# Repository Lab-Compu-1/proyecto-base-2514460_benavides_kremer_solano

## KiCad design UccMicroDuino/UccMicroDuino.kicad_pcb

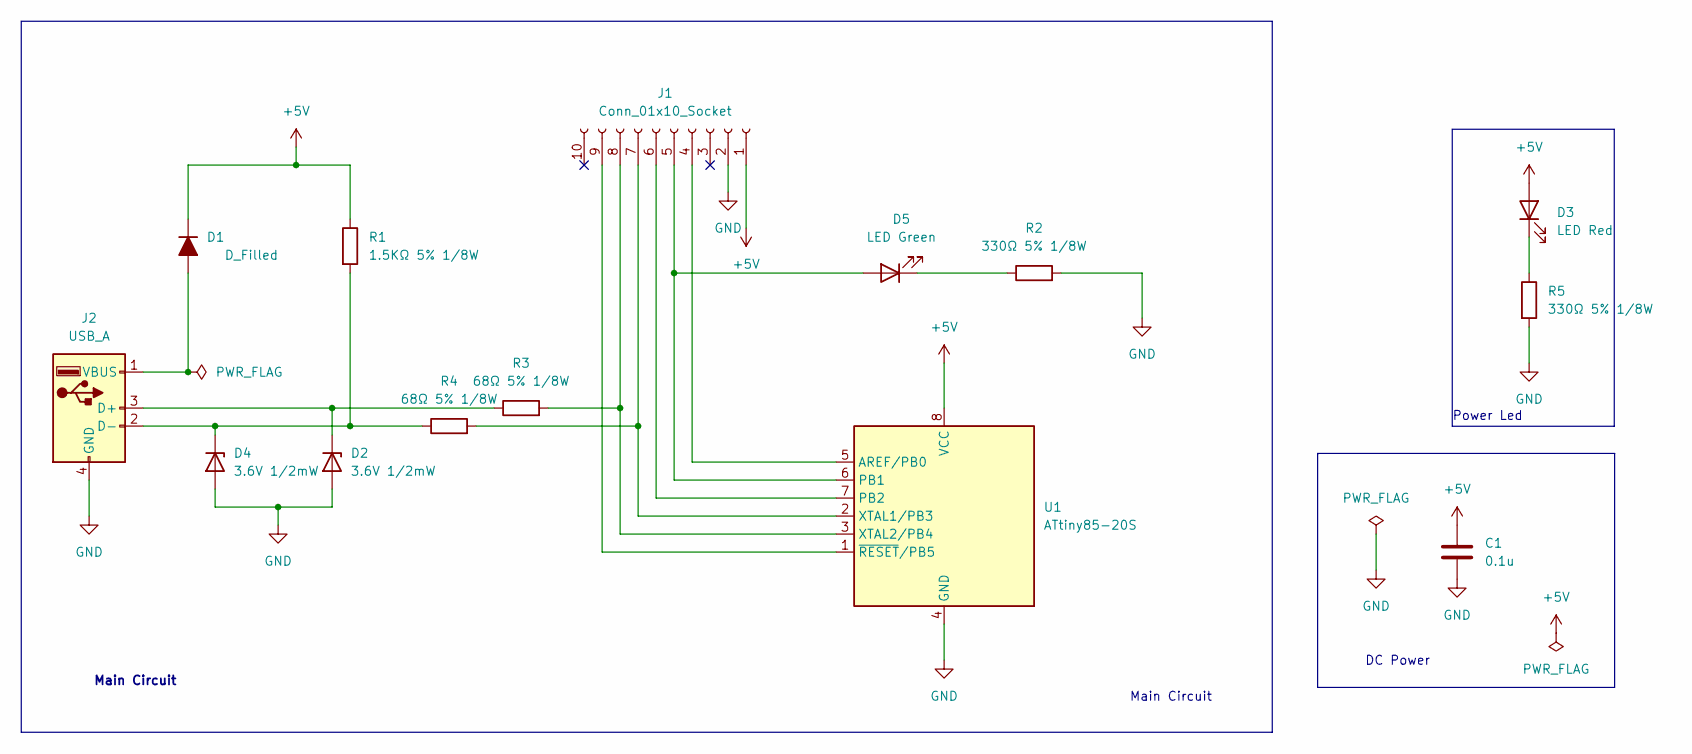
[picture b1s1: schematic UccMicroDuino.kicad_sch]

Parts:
C1: 0.1u; C_0805_2012Metric_Pad1.18x1.45mm_HandSolder
D1: D_Filled; D_MiniMELF
D2, D4: 3.6V 1/2mW; D_SOD-123
D3: LED Red; ledSMD
D5: LED Green; ledSMD
J1: Conn_01x10_Socket; PinHeader_1x10_P2.54mm_Vertical
J2: USB_A; USB_A_UCC
R1: 1.5KΩ 5% 1/8W; R_0805_2012Metric_Pad1.20x1.40mm_HandSolder
R2, R5: 330Ω 5% 1/8W; R_0805_2012Metric_Pad1.20x1.40mm_HandSolder
R3, R4: 68Ω 5% 1/8W; R_0805_2012Metric_Pad1.20x1.40mm_HandSolder
U1: ATtiny85-20S; SOIC-8_5.3x5.3mm_P1.27mm

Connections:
+5V: C1.1, D1.1 (K), D3.2 (A), J1.1, R1.1, U1.8 (VCC)
GND: C1.2, D2.2 (A), D4.2 (A), J1.2, J2.4 (GND), R2.2, R5.2, U1.4 (GND)
unnamed: D1.2 (A), J2.1 (VBUS)
unnamed: D2.1 (K), J2.3 (D+), R3.1
unnamed: D3.1 (K), R5.1
unnamed: D4.1 (K), J2.2 (D-), R1.2, R4.1
unnamed: D5.2 (A), J1.5, U1.6 (PB1)
unnamed: D5.1 (K), R2.1
unnamed: J1.4, U1.5 (AREF/PB0)
unnamed: J1.6, U1.7 (PB2)
unnamed: J1.7, R4.2, U1.2 (XTAL1/PB3)
unnamed: J1.8, R3.2, U1.3 (XTAL2/PB4)
unnamed: J1.9, U1.1 (~RESET/PB5)

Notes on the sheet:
Main Circuit
Power Led
DC Power

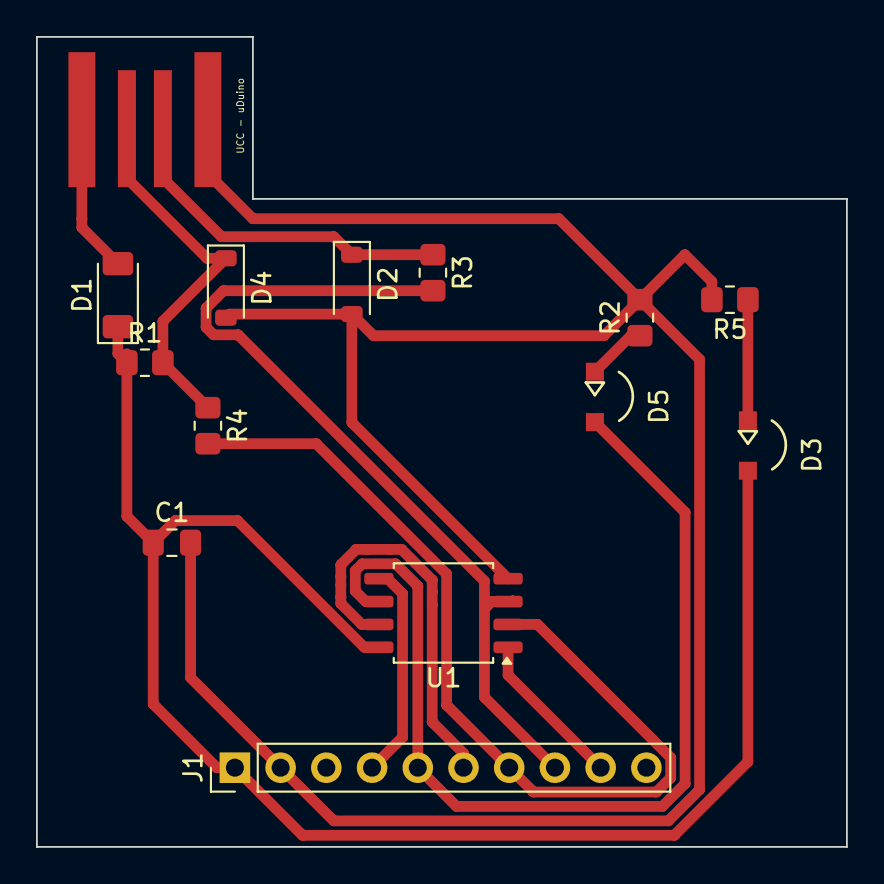
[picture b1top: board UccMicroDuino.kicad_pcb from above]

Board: 2 copper layers, 45.0 x 45.0 mm, 14 parts (0 on the bottom side), 13 nets.

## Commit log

2025-04-14 Setting up GitHub Classroom Feedback
2025-04-14 GitHub Classroom Feedback
2025-04-14 first class
2025-04-14 fix push
2025-04-21 footprint schematic
2025-04-28 cuts, checks and idk
